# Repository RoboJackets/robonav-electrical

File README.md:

RoboNav Electrical
==========
Welcome to the electrcial repository of the RoboNav team! 

## Recommended Software (free)
- a [github account](https://github.com/join?source=header-home) 
    - the centralized location for all common files
- [git](https://git-scm.com/downloads)
    - popular version control system
    - quick [tutorial](https://try.github.io/levels/1/challenges/1)
- [EAGLE](https://www.autodesk.com/education/free-software/eagle)
    - CAD software for designing printed circuit boards (PCBs)

## Cloning the Repository
Now that you have all the required software, it's time to clone the repo!

To clone the repo, nagivate to the location in your computer where you would
like the repository using the change directory command in your terminal (cd):

```
cd desired-location
```

Now its time to clone:

```
git clone https://github.com/RoboJackets/robonav-electrical.git
```

You now have all you need to start contributing to the RoboNav Electrical team!

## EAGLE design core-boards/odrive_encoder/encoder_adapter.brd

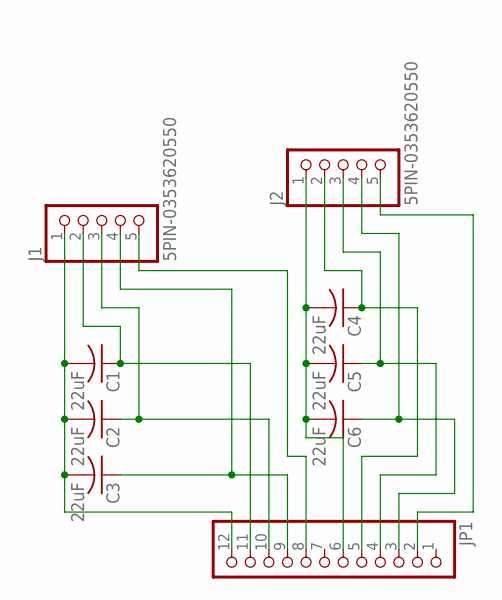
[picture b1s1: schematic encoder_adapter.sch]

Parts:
C1, C2, C3, C4, C5, C6: 22uF; C0805
J1, J2: 5PIN-0353620550; 0353620550
JP1: PINHD-1X12; 1X12

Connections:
unnamed: C1.2, C2.2, C3.2, J1.1, JP1.12
unnamed: C3.1, J1.4, JP1.9
unnamed: C1.1, J1.2, JP1.11
unnamed: C2.1, J1.3, JP1.10
unnamed: C4.1, J2.2, JP1.5
unnamed: C5.1, J2.3, JP1.4
unnamed: C6.1, J2.4, JP1.3
unnamed: J2.5, JP1.2
unnamed: J1.5, JP1.8
unnamed: C4.2, C5.2, C6.2, J2.1, JP1.6

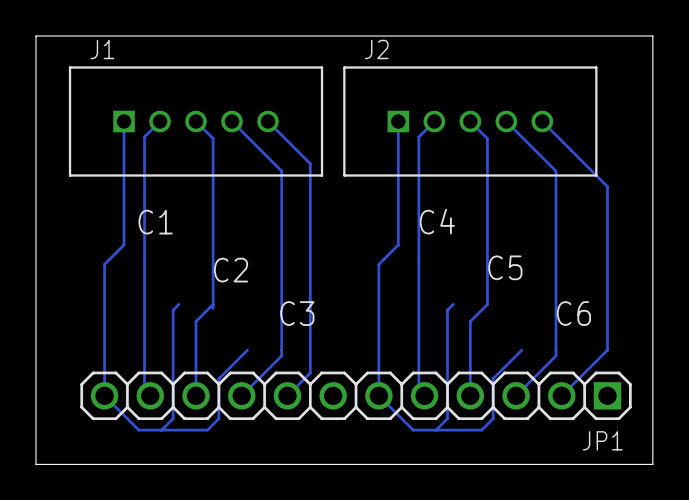
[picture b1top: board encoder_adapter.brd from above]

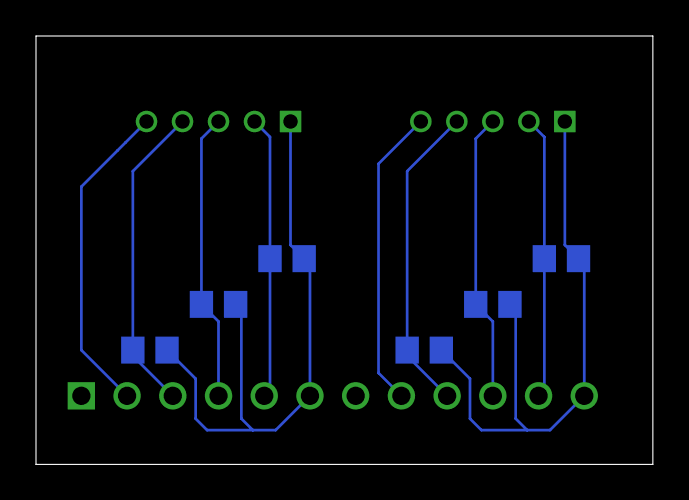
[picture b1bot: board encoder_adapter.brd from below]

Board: 1 copper layer, 34.3 x 23.8 mm, 9 parts (6 on the bottom side), 10 nets.

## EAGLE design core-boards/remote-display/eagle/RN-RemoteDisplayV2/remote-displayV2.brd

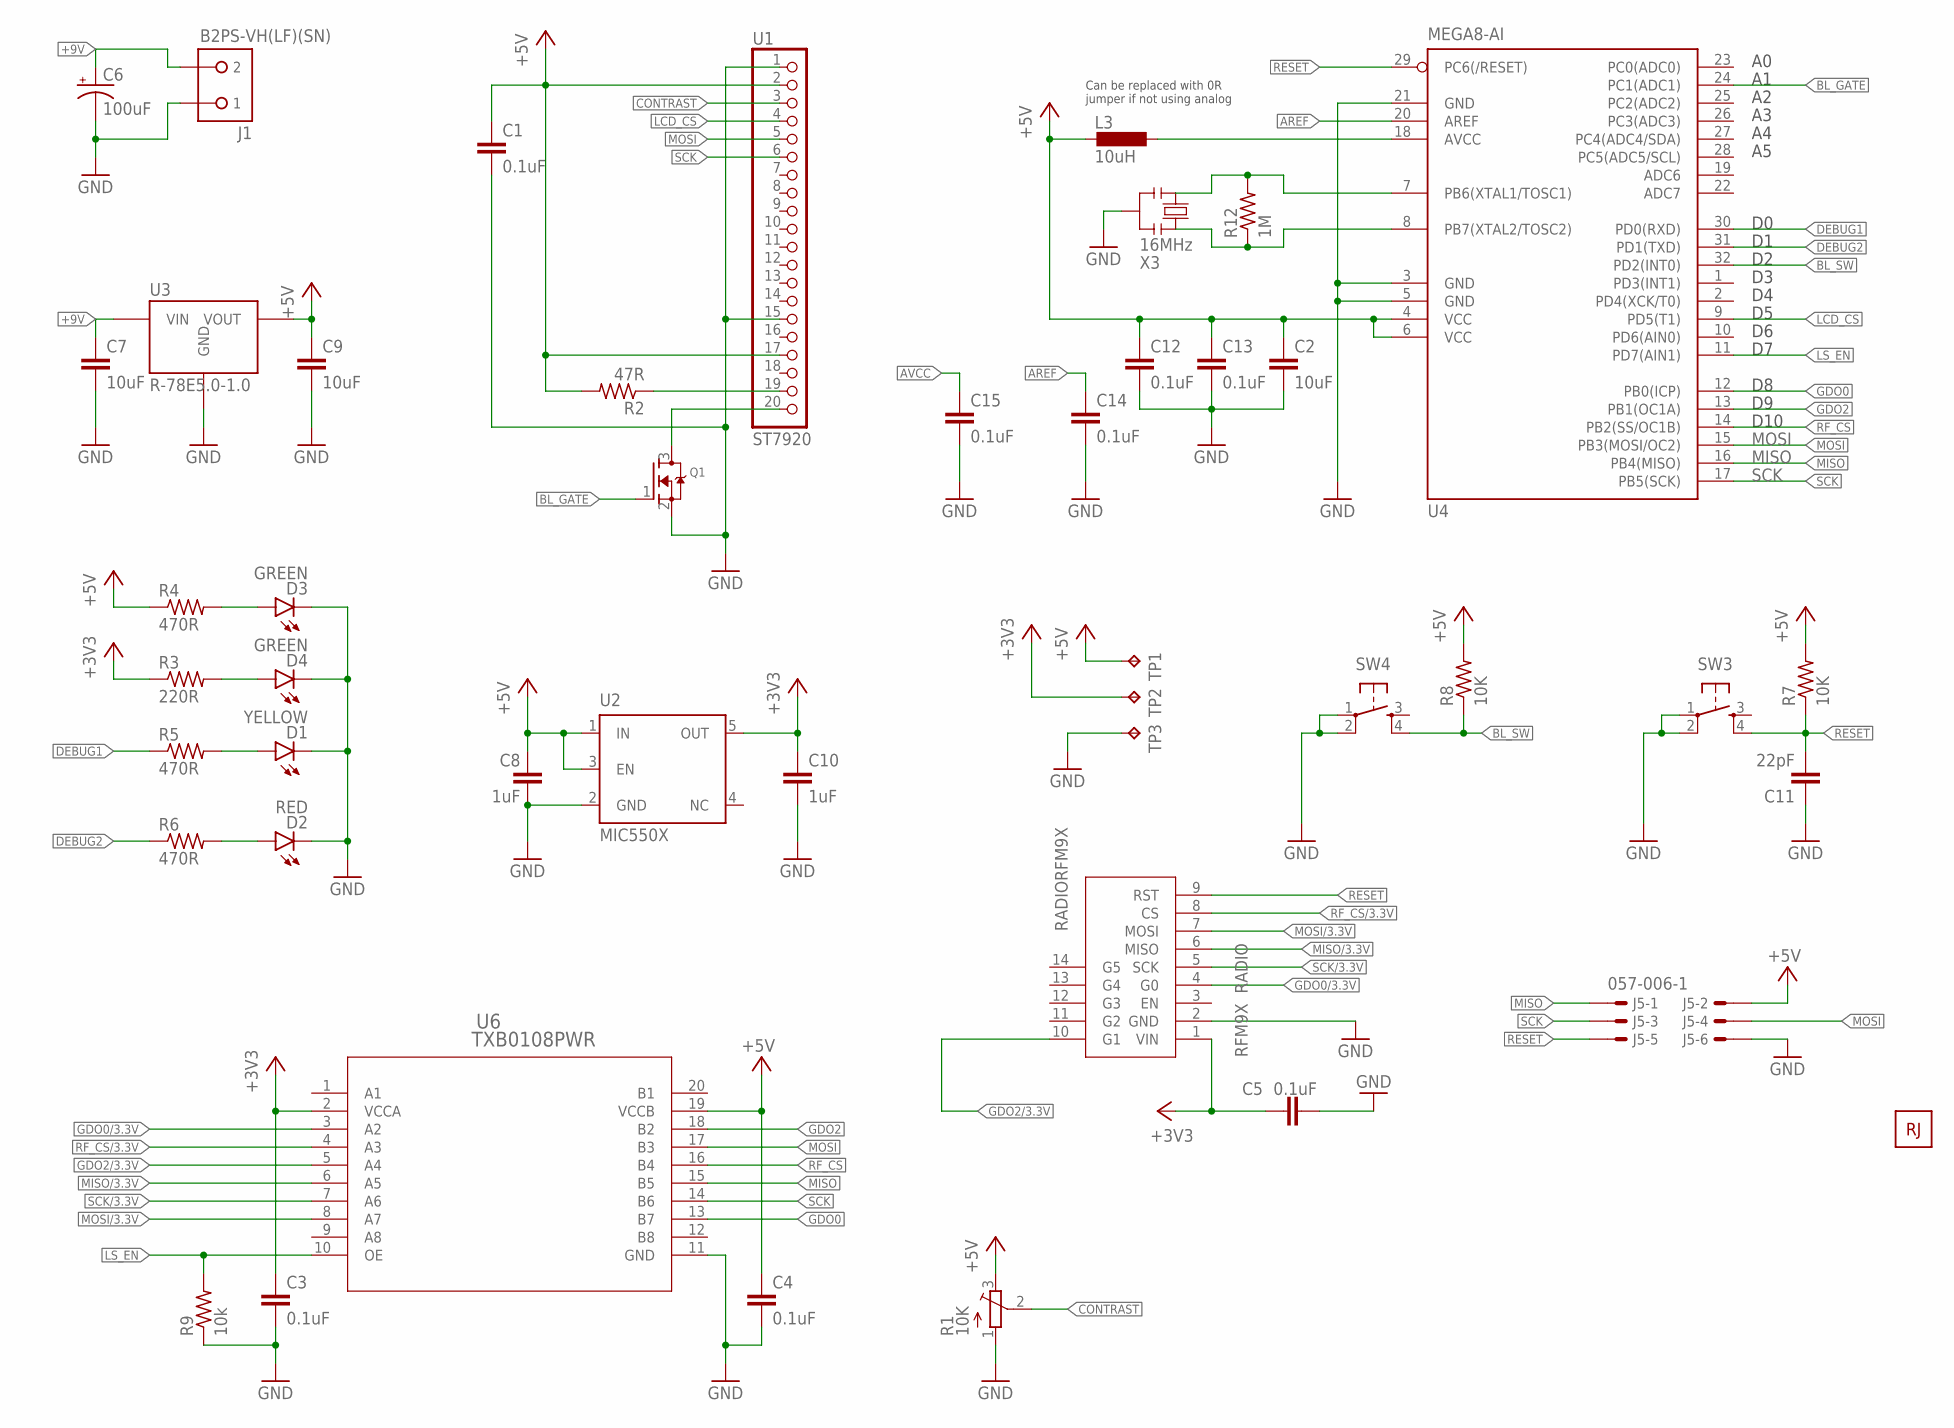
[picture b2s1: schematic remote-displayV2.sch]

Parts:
C1, C3, C4, C5, C12, C13, C14, C15: 0.1uF; C0603
C2: 10uF; C0805
C6: 100uF; E5-10,5
C7, C9: 10uF; C0603
C8, C10: 1uF; C0603
C11: 22pF; C0603
D1: YELLOW; LED3MM
D2: RED; LED3MM
D3, D4: GREEN; LED3MM
J1: B2PS-VH(LF)(SN); B2PS-CENTERED
J5: 057-006-1; DIGIKEY 3M15451-ND
L3: 10uH; 0805
Q1: MOSFET-NREFLOW; SOT23
R1: 10K; TRIM-3386
R2: 47R; R0805
R3: 220R; R0603
R4, R5, R6: 470R; R0603
R7, R8: 10K; R0603
R9: 10k; R0603
R12: 1M; R0603
SW3, SW4: TL1105_A-H
TP1, TP2, TP3: TPPAD1-17; P1-17
U1: ST7920; ST7920-LCD
U2: MIC550X; SOT23-DBV
U3: R-78E5.0-1.0; R-78E
U4: MEGA8-AI; TQFP32-08
U6: TXB0108PWR; PW20
U$1: RADIORFM9X; RFM9X
U$2: ROBOBUZZ1.0X; ROBOBUZZ_1.0X
X3: 16MHz; RESONATOR

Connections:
!RESET: C11.2, J5.5, R7.1, SW3.4, U4.29 (PC6(/RESET)), U$1.9 (RST)
!RF_CS!: U4.14 (PB2(SS/OC1B)), U6.16 (B4)
!RF_CS!/3.3V: U6.4 (A3), U$1.8 (CS)
+3V3: C3.1, C5.1, C10.1, R3.1, TP2.TP, U2.5 (OUT), U6.2 (VCCA), U$1.1 (VIN)
+5V: C1.1, C2.1, C4.1, C8.1, C9.1, C12.1, C13.1, J5.2, L3.2, R1.3 (E), R2.2, R4.1, R7.2, R8.2, TP1.TP, U1.2, U1.17, U2.1 (IN), U2.3 (EN), U3.3 (VOUT), U4.4 (VCC), U4.6 (VCC), U6.19 (VCCB)
+9V: C6.+, C7.1, J1.2, U3.1 (VIN)
AREF: C14.1, U4.20 (AREF)
AVCC: C15.1, L3.1, U4.18 (AVCC)
BL_DRAIN: Q1.3 (D), U1.20
BL_GATE: Q1.1 (G), U4.24 (PC1(ADC1))
BL_SW: R8.1, SW4.4, U4.32 (PD2(INT0))
CONTRAST: R1.2 (S), U1.3
DEBUG1: R5.1, U4.30 (PD0(RXD))
DEBUG2: R6.1, U4.31 (PD1(TXD))
GDO0: U4.12 (PB0(ICP)), U6.13 (B7)
GDO0/3.3V: U6.3 (A2), U$1.4 (G0)
GDO2: U4.13 (PB1(OC1A)), U6.18 (B2)
GDO2/3.3V: U6.5 (A4), U$1.10 (G1)
GND: C1.2, C2.2, C3.2, C4.2, C5.2, C6.-, C7.2, C8.2, C9.2, C10.2, C11.1, C12.2, C13.2, C14.2, C15.2, D1.K (C), D2.K (C), D3.K (C), D4.K (C), J1.1, J5.6, Q1.2 (S), R1.1 (A), R9.1, SW3.1, SW3.2, SW4.1, SW4.2, TP3.TP, U1.1, U1.15, U2.2 (GND), U3.2 (GND), U4.3 (GND), U4.5 (GND), U4.21 (GND), U6.11 (GND), U$1.2 (GND), X3.2
LCD_BL: R2.1, U1.19
LCD_CS: U1.4, U4.9 (PD5(T1))
LS_EN: R9.2, U4.11 (PD7(AIN1)), U6.10 (OE)
MISO: J5.1, U4.16 (PB4(MISO)), U6.15 (B5)
MISO/3.3V: U6.6 (A5), U$1.6 (MISO)
MOSI: J5.4, U1.5, U4.15 (PB3(MOSI/OC2)), U6.17 (B3)
MOSI/3.3V: U6.8 (A7), U$1.7 (MOSI)
PWR_LED: D3.A, R4.2
PWR_LED1: D4.A, R3.2
SCK: J5.3, U1.6, U4.17 (PB5(SCK)), U6.14 (B6)
SCK/3.3V: U6.7 (A6), U$1.5 (SCK)
STAT1_LED: D1.A, R5.2
STAT2_LED: D2.A, R6.2
XTAL1: R12.2, U4.7 (PB6(XTAL1/TOSC1)), X3.1
XTAL2: R12.1, U4.8 (PB7(XTAL2/TOSC2)), X3.3

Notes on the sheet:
D10
Can be replaced with 0R jumper if not using analog

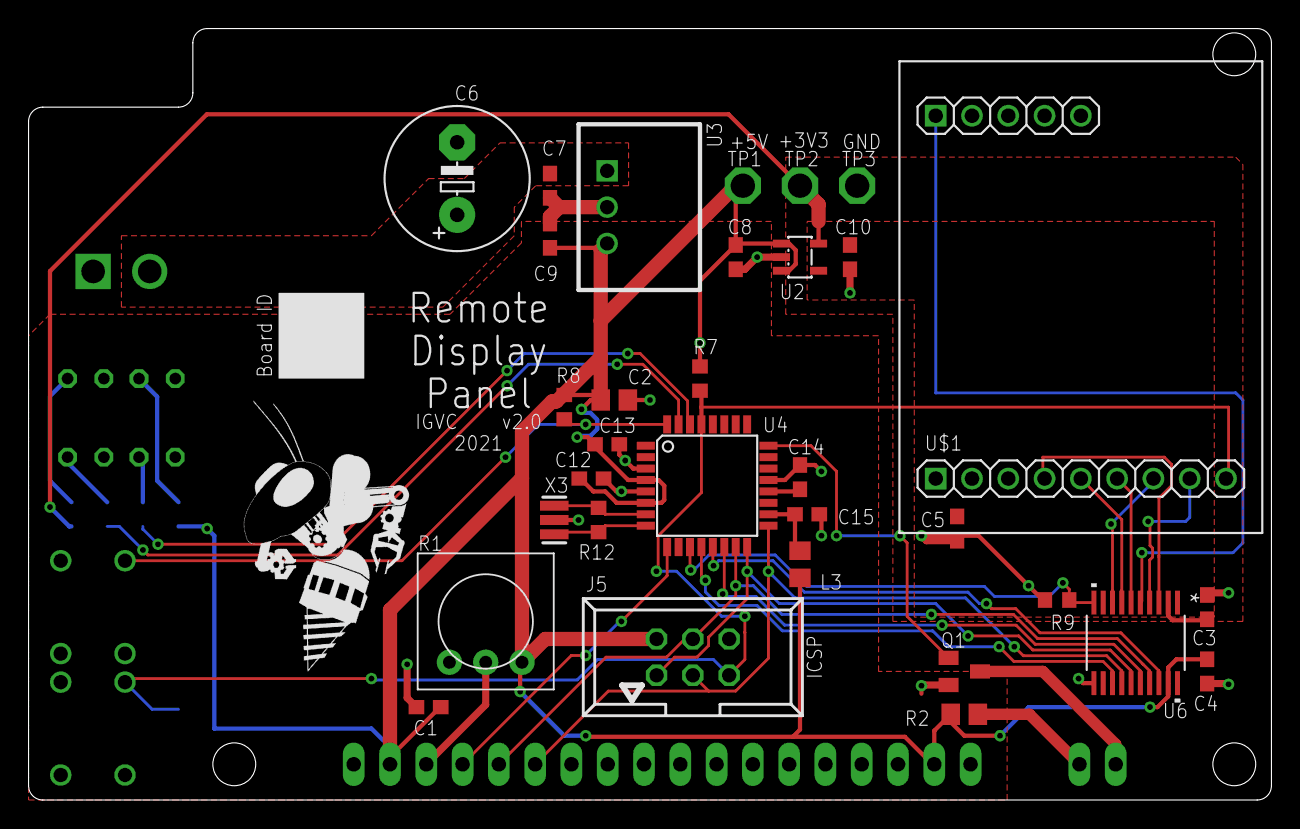
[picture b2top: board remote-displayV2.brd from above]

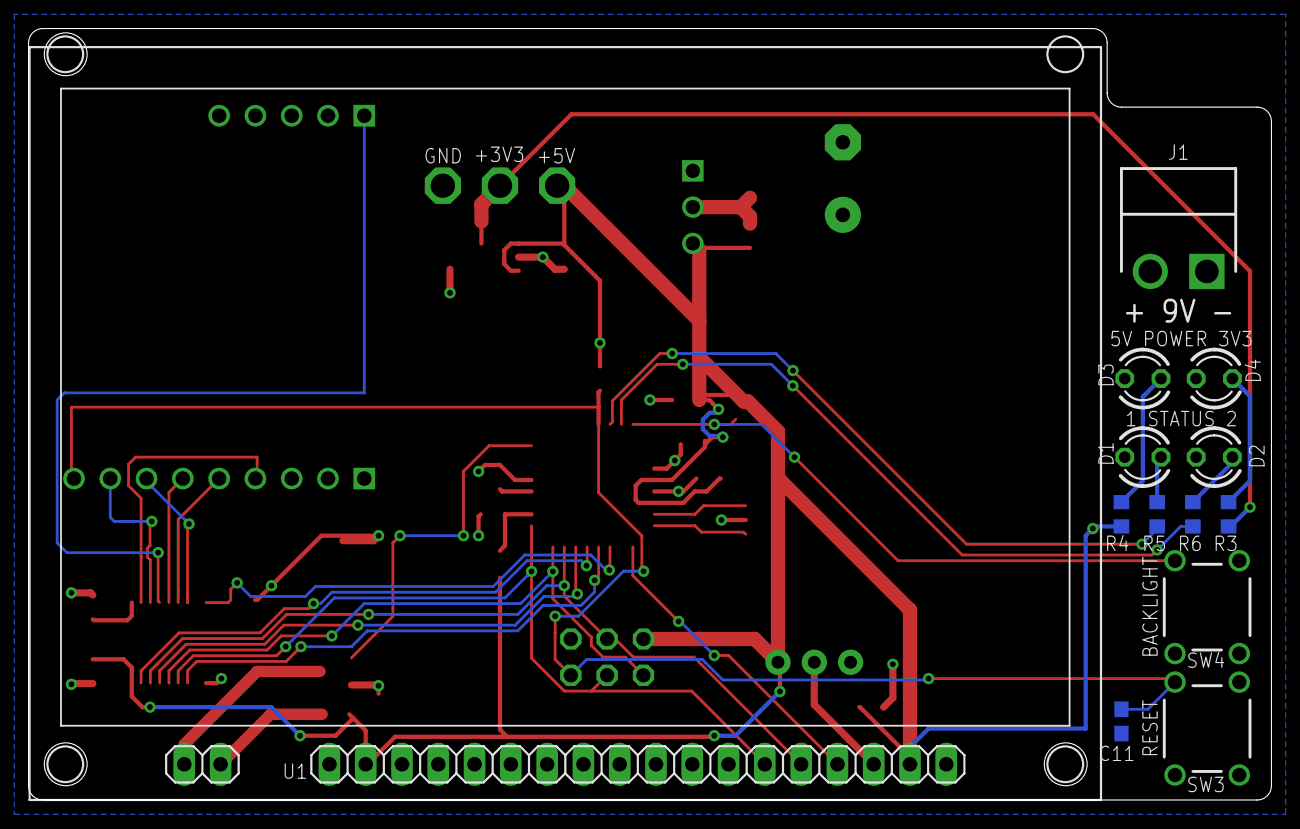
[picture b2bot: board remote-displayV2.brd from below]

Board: 2 copper layers, 87.0 x 54.0 mm, 46 parts (13 on the bottom side), 34 nets.

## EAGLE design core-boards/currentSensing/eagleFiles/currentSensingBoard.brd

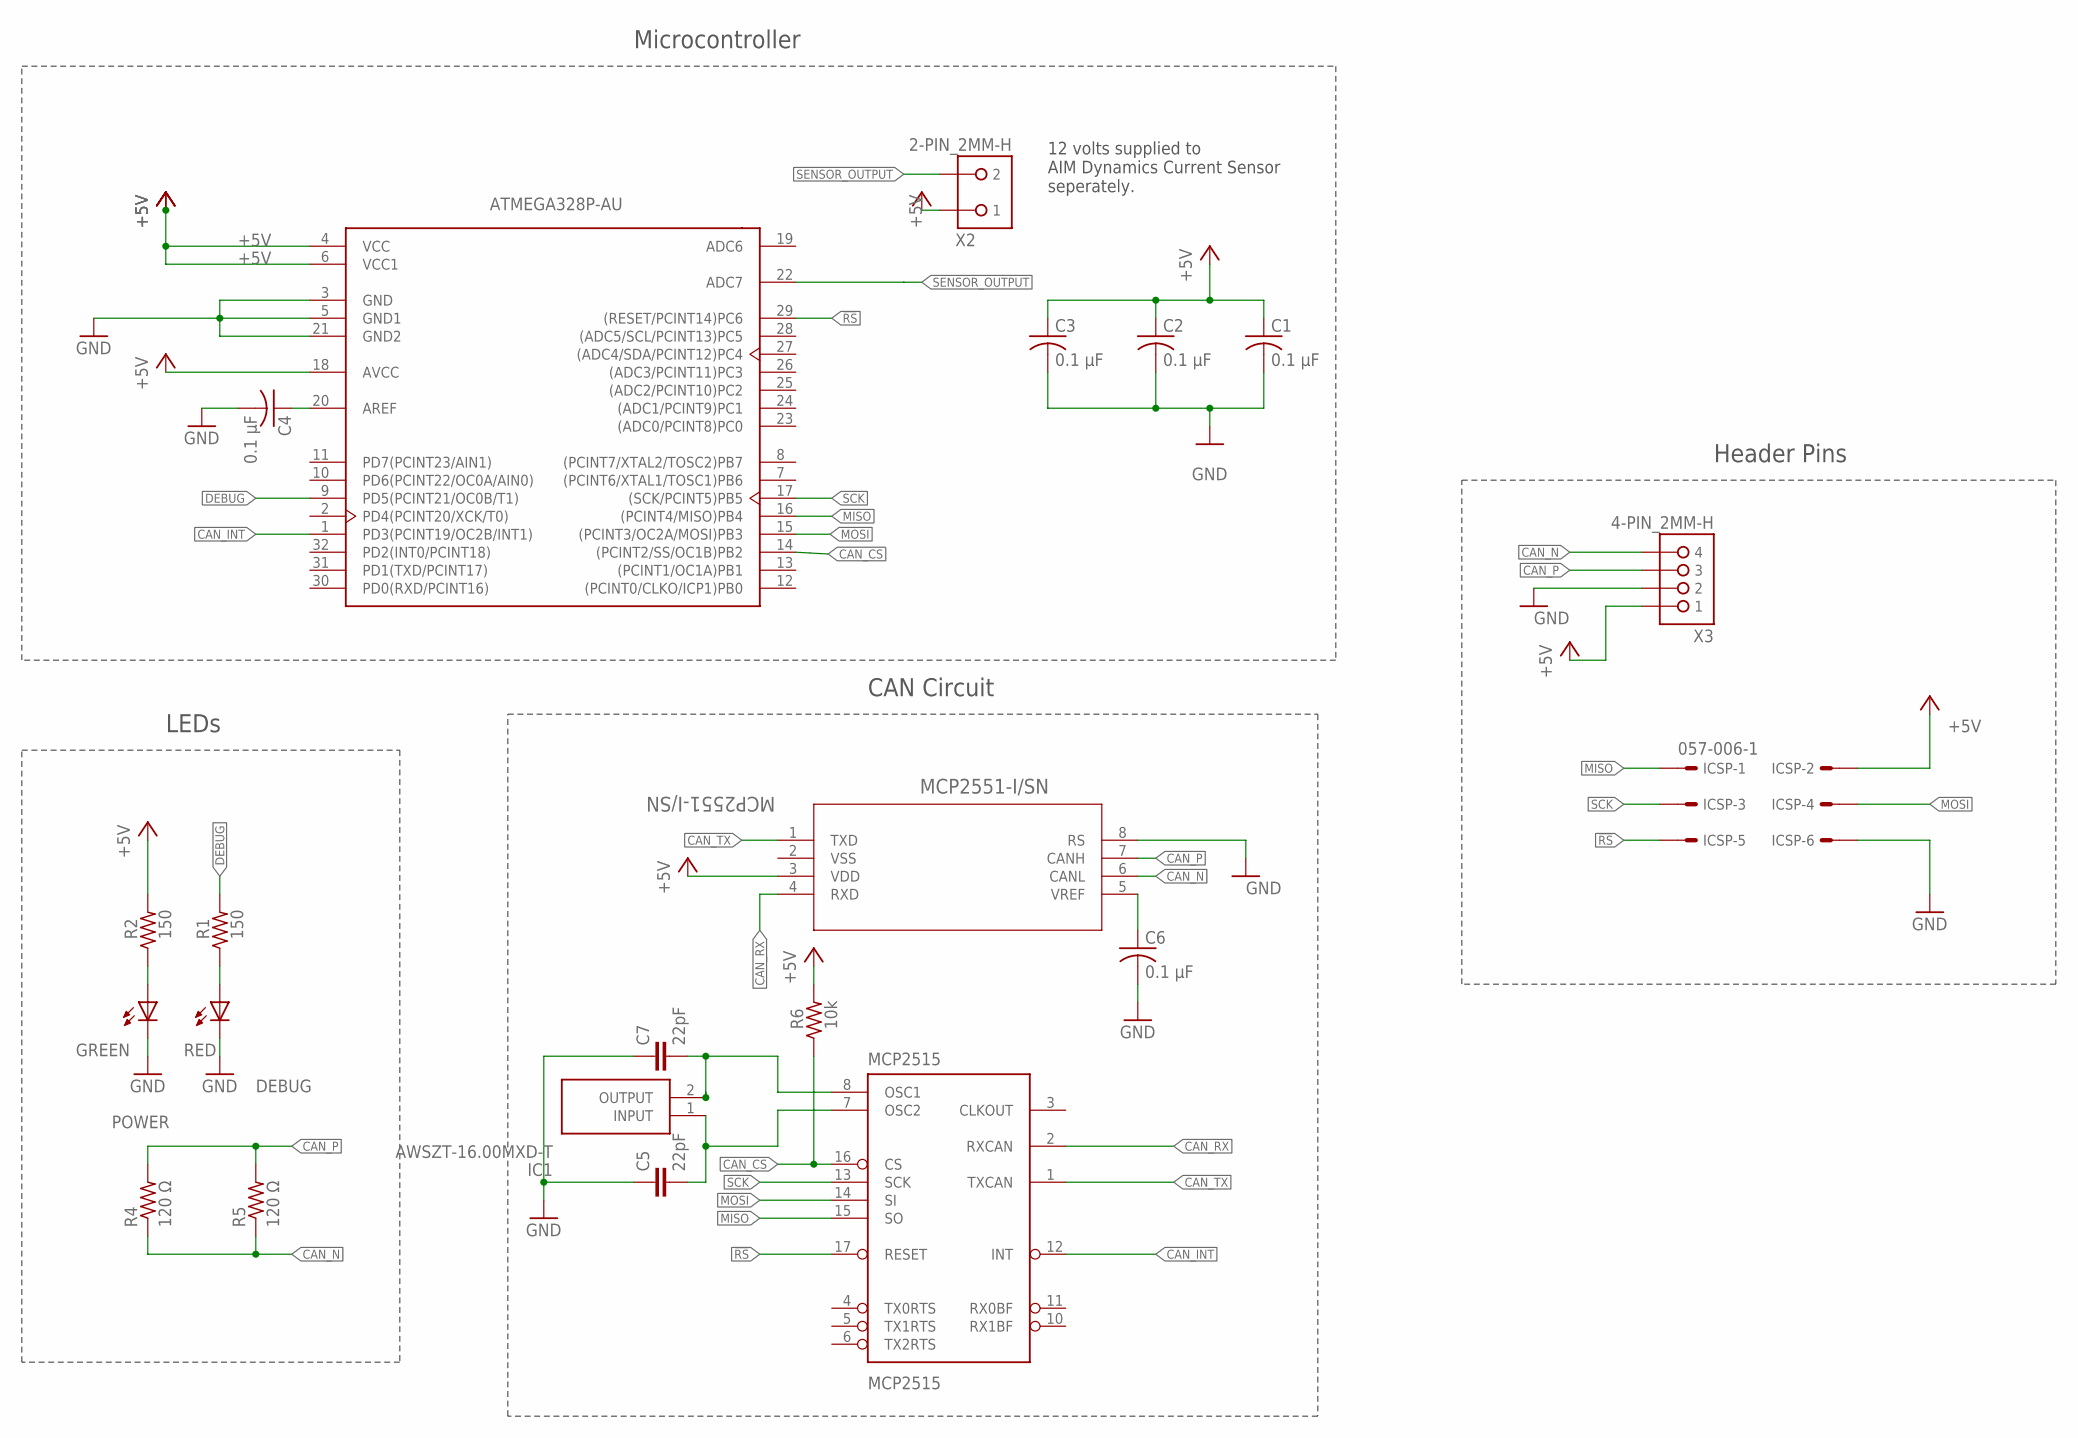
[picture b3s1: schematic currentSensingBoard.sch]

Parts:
ATMEGA328P-AU(V1): ATMEGA328P-AU (V1); TQFP-32; PARTS_NAME ATMEGA328P-AU
C1, C2, C3, C4, C6: 0.1 µF; C0603
C5, C7: 22pF; 0603-CAP
DEBUG: RED; CHIP-LED0603
IC1: AWSZT-16.00MXD-T; AWSZT1600MXDT
ICSP: 057-006-1
MCP2515: MCP2515; SO-18W
MCP2551-I/SN: MCP2551-I/SN; SOIC8-N_MC
POWER: GREEN; CHIP-LED0603
R1, R2: 150; R0603
R4, R5: 120 Ω; R0603
R6: 10k; R0603
X2: 2-PIN_2MM-H; 2MM-2-H
X3: 4-PIN_2MM-H; 2MM-4-H

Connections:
!RS: ATMEGA328P-AU(V1).29 ((RESET/PCINT14)PC6), ICSP.5, MCP2515.17 (RESET)
+5V: ATMEGA328P-AU(V1).4 (VCC), ATMEGA328P-AU(V1).6 (VCC1), ATMEGA328P-AU(V1).18 (AVCC), C1.1, C2.1, C3.1, ICSP.2, MCP2551-I/SN.3 (VDD), R2.2, R6.2, X2.1, X3.1
CAN_CS: ATMEGA328P-AU(V1).14 ((PCINT2/SS/OC1B)PB2), MCP2515.16 (CS), R6.1
CAN_INT: ATMEGA328P-AU(V1).1 (PD3(PCINT19/OC2B/INT1)), MCP2515.12 (INT)
CAN_N: MCP2551-I/SN.6 (CANL), R4.1, R5.1, X3.4
CAN_P: MCP2551-I/SN.7 (CANH), R4.2, R5.2, X3.3
CAN_RX: MCP2515.2 (RXCAN), MCP2551-I/SN.4 (RXD)
CAN_TX: MCP2515.1 (TXCAN), MCP2551-I/SN.1 (TXD)
CLK1: C5.2, IC1.1 (INPUT), MCP2515.7 (OSC2)
CLK2: C7.2, IC1.2 (OUTPUT), MCP2515.8 (OSC1)
DEBUG: ATMEGA328P-AU(V1).9 (PD5(PCINT21/OC0B/T1)), R1.2
GND: ATMEGA328P-AU(V1).3 (GND), ATMEGA328P-AU(V1).5 (GND1), ATMEGA328P-AU(V1).21 (GND2), C1.2, C2.2, C3.2, C4.2, C5.1, C6.2, C7.1, DEBUG.C (K), ICSP.6, MCP2551-I/SN.8 (RS), POWER.C (K), X3.2
MISO: ATMEGA328P-AU(V1).16 ((PCINT4/MISO)PB4), ICSP.1, MCP2515.15 (SO)
MOSI: ATMEGA328P-AU(V1).15 ((PCINT3/OC2A/MOSI)PB3), ICSP.4, MCP2515.14 (SI)
unnamed: DEBUG.A, R1.1
unnamed: C6.1, MCP2551-I/SN.5 (VREF)
unnamed: ATMEGA328P-AU(V1).20 (AREF), C4.1
unnamed: POWER.A, R2.1
SCK: ATMEGA328P-AU(V1).17 ((SCK/PCINT5)PB5), ICSP.3, MCP2515.13 (SCK)
SENSOR_OUTPUT: ATMEGA328P-AU(V1).22 (ADC7), X2.2
VDD: MCP2515.18 (VDD)
VSS: MCP2515.9 (VSS)

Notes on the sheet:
CAN Circuit
12 volts supplied to AIM Dynamics Current Sensor seperately.
LEDs
Header Pins
Microcontroller

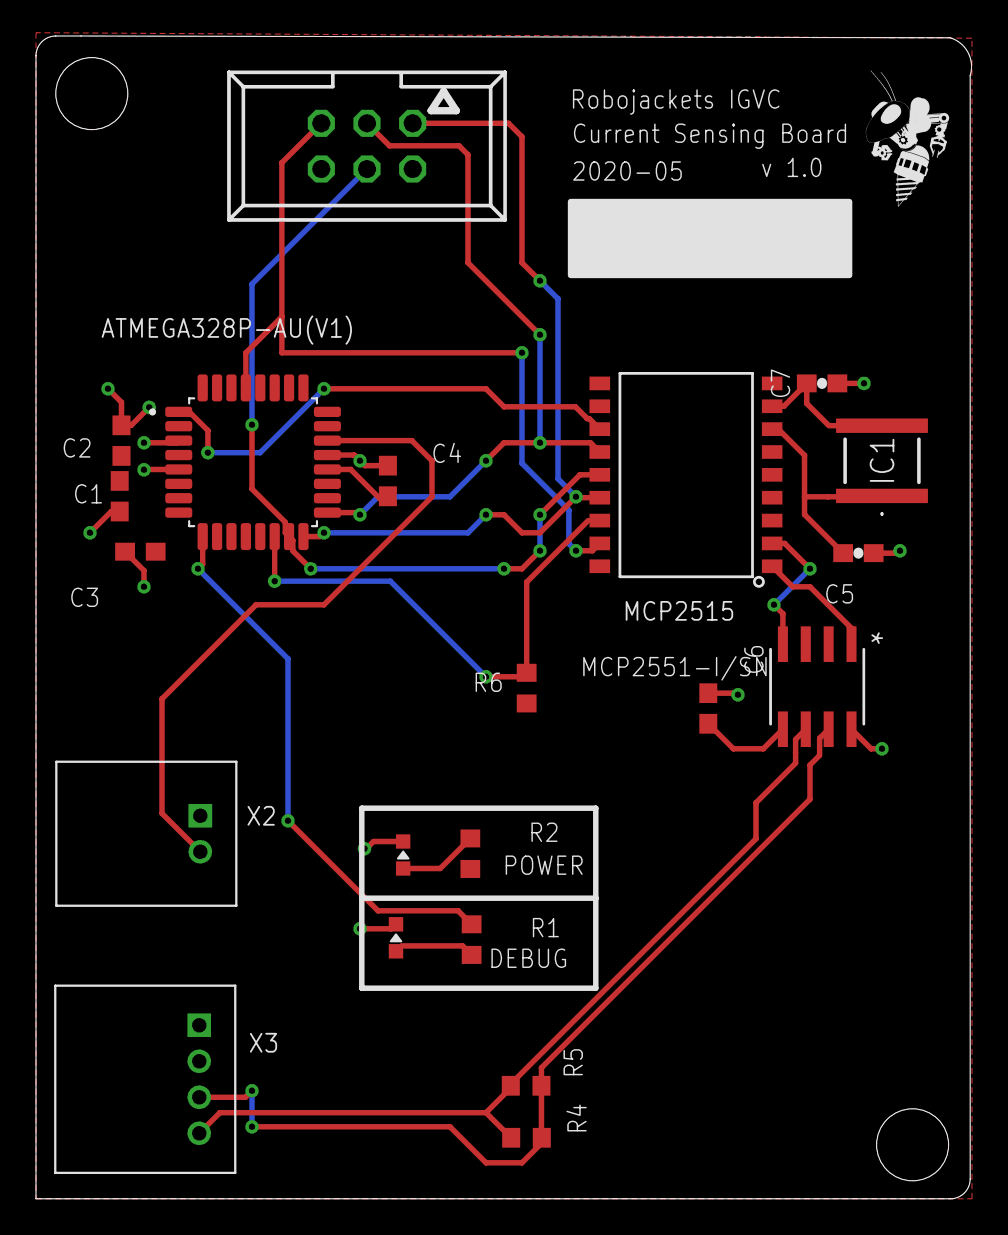
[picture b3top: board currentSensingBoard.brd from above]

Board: 2 copper layers, 52.0 x 64.6 mm, 22 parts (0 on the bottom side), 20 nets.

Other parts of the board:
U$1: ROBOBUZZ_0.4X

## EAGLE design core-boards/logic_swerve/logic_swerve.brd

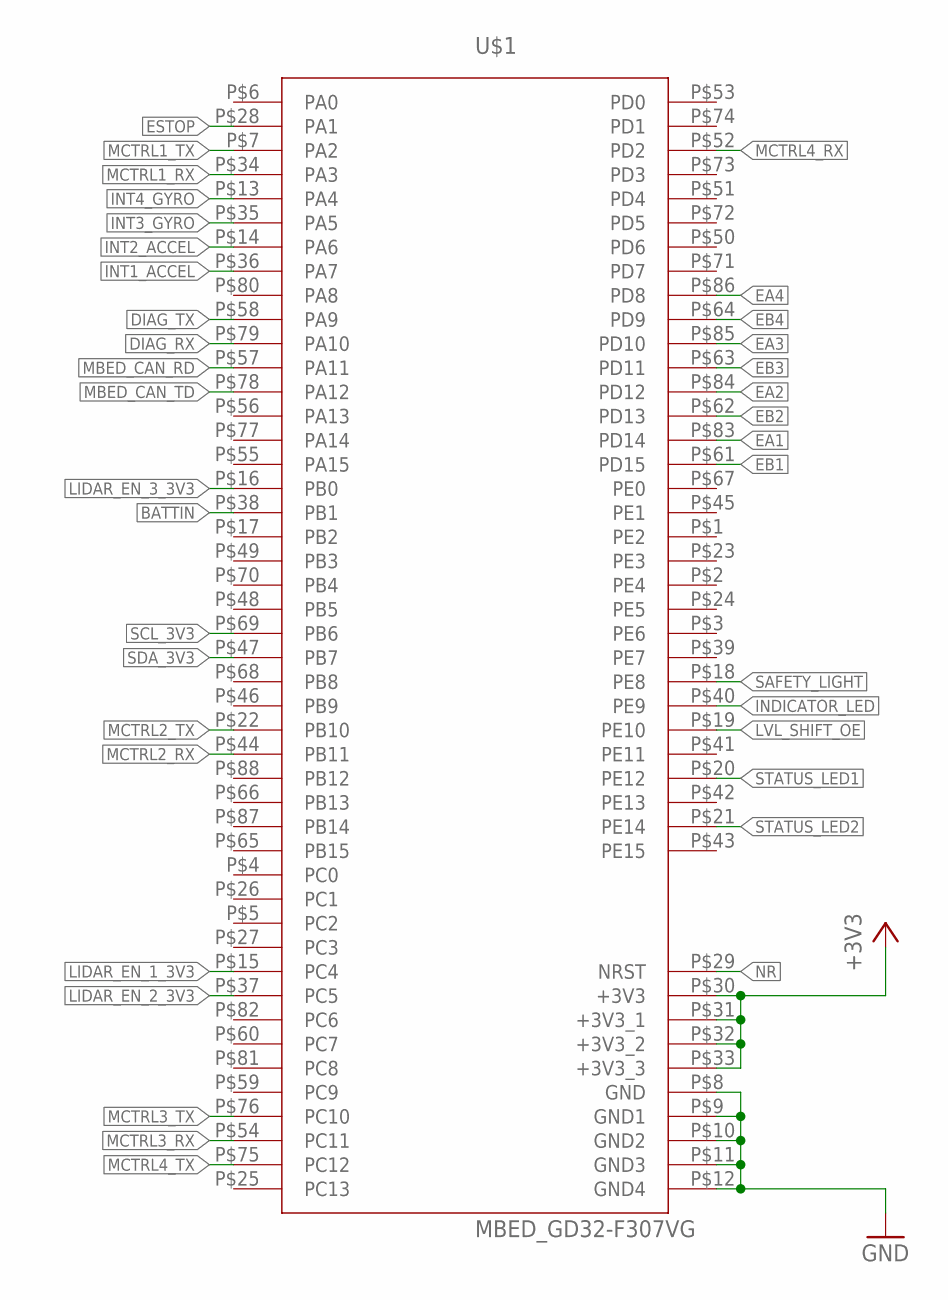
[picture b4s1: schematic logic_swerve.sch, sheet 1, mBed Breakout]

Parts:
U$1: MBED_GD32-F307VG; SWERVE_MBED

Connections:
+3V3: U$1.P$30 (+3V3), U$1.P$31 (+3V3_1), U$1.P$32 (+3V3_2), U$1.P$33 (+3V3_3); also elsewhere on the board
BATTIN: U$1.P$38 (PB1); also elsewhere on the board
DIAG_RX: U$1.P$79 (PA10); also elsewhere on the board
DIAG_TX: U$1.P$58 (PA9); also elsewhere on the board
EA1: U$1.P$83 (PD14); also elsewhere on the board
EA2: U$1.P$84 (PD12); also elsewhere on the board
EA3: U$1.P$85 (PD10); also elsewhere on the board
EA4: U$1.P$86 (PD8); also elsewhere on the board
EB1: U$1.P$61 (PD15); also elsewhere on the board
EB2: U$1.P$62 (PD13); also elsewhere on the board
EB3: U$1.P$63 (PD11); also elsewhere on the board
EB4: U$1.P$64 (PD9); also elsewhere on the board
ESTOP: U$1.P$28 (PA1); also elsewhere on the board
GND: U$1.P$8 (GND), U$1.P$9 (GND1), U$1.P$10 (GND2), U$1.P$11 (GND3), U$1.P$12 (GND4); also elsewhere on the board
INDICATOR_LED: U$1.P$40 (PE9); also elsewhere on the board
INT1_ACCEL: U$1.P$36 (PA7)
INT2_ACCEL: U$1.P$14 (PA6)
INT3_GYRO: U$1.P$35 (PA5)
INT4_GYRO: U$1.P$13 (PA4)
LIDAR_EN_1_3V3: U$1.P$15 (PC4); also elsewhere on the board
LIDAR_EN_2_3V3: U$1.P$37 (PC5); also elsewhere on the board
LIDAR_EN_3_3V3: U$1.P$16 (PB0); also elsewhere on the board
LVL_SHIFT_OE: U$1.P$19 (PE10); also elsewhere on the board
MBED_CAN_RD: U$1.P$57 (PA11); also elsewhere on the board
MBED_CAN_TD: U$1.P$78 (PA12); also elsewhere on the board
MCTRL1_RX: U$1.P$34 (PA3); also elsewhere on the board
MCTRL1_TX: U$1.P$7 (PA2); also elsewhere on the board
MCTRL2_RX: U$1.P$44 (PB11); also elsewhere on the board
MCTRL2_TX: U$1.P$22 (PB10); also elsewhere on the board
MCTRL3_RX: U$1.P$54 (PC11); also elsewhere on the board
MCTRL3_TX: U$1.P$76 (PC10); also elsewhere on the board
MCTRL4_RX: U$1.P$52 (PD2); also elsewhere on the board
MCTRL4_TX: U$1.P$75 (PC12); also elsewhere on the board
NR: U$1.P$29 (NRST); also elsewhere on the board
SAFETY_LIGHT: U$1.P$18 (PE8); also elsewhere on the board
SCL_3V3: U$1.P$69 (PB6); also elsewhere on the board
SDA_3V3: U$1.P$47 (PB7); also elsewhere on the board
STATUS_LED1: U$1.P$20 (PE12); also elsewhere on the board
STATUS_LED2: U$1.P$21 (PE14); also elsewhere on the board

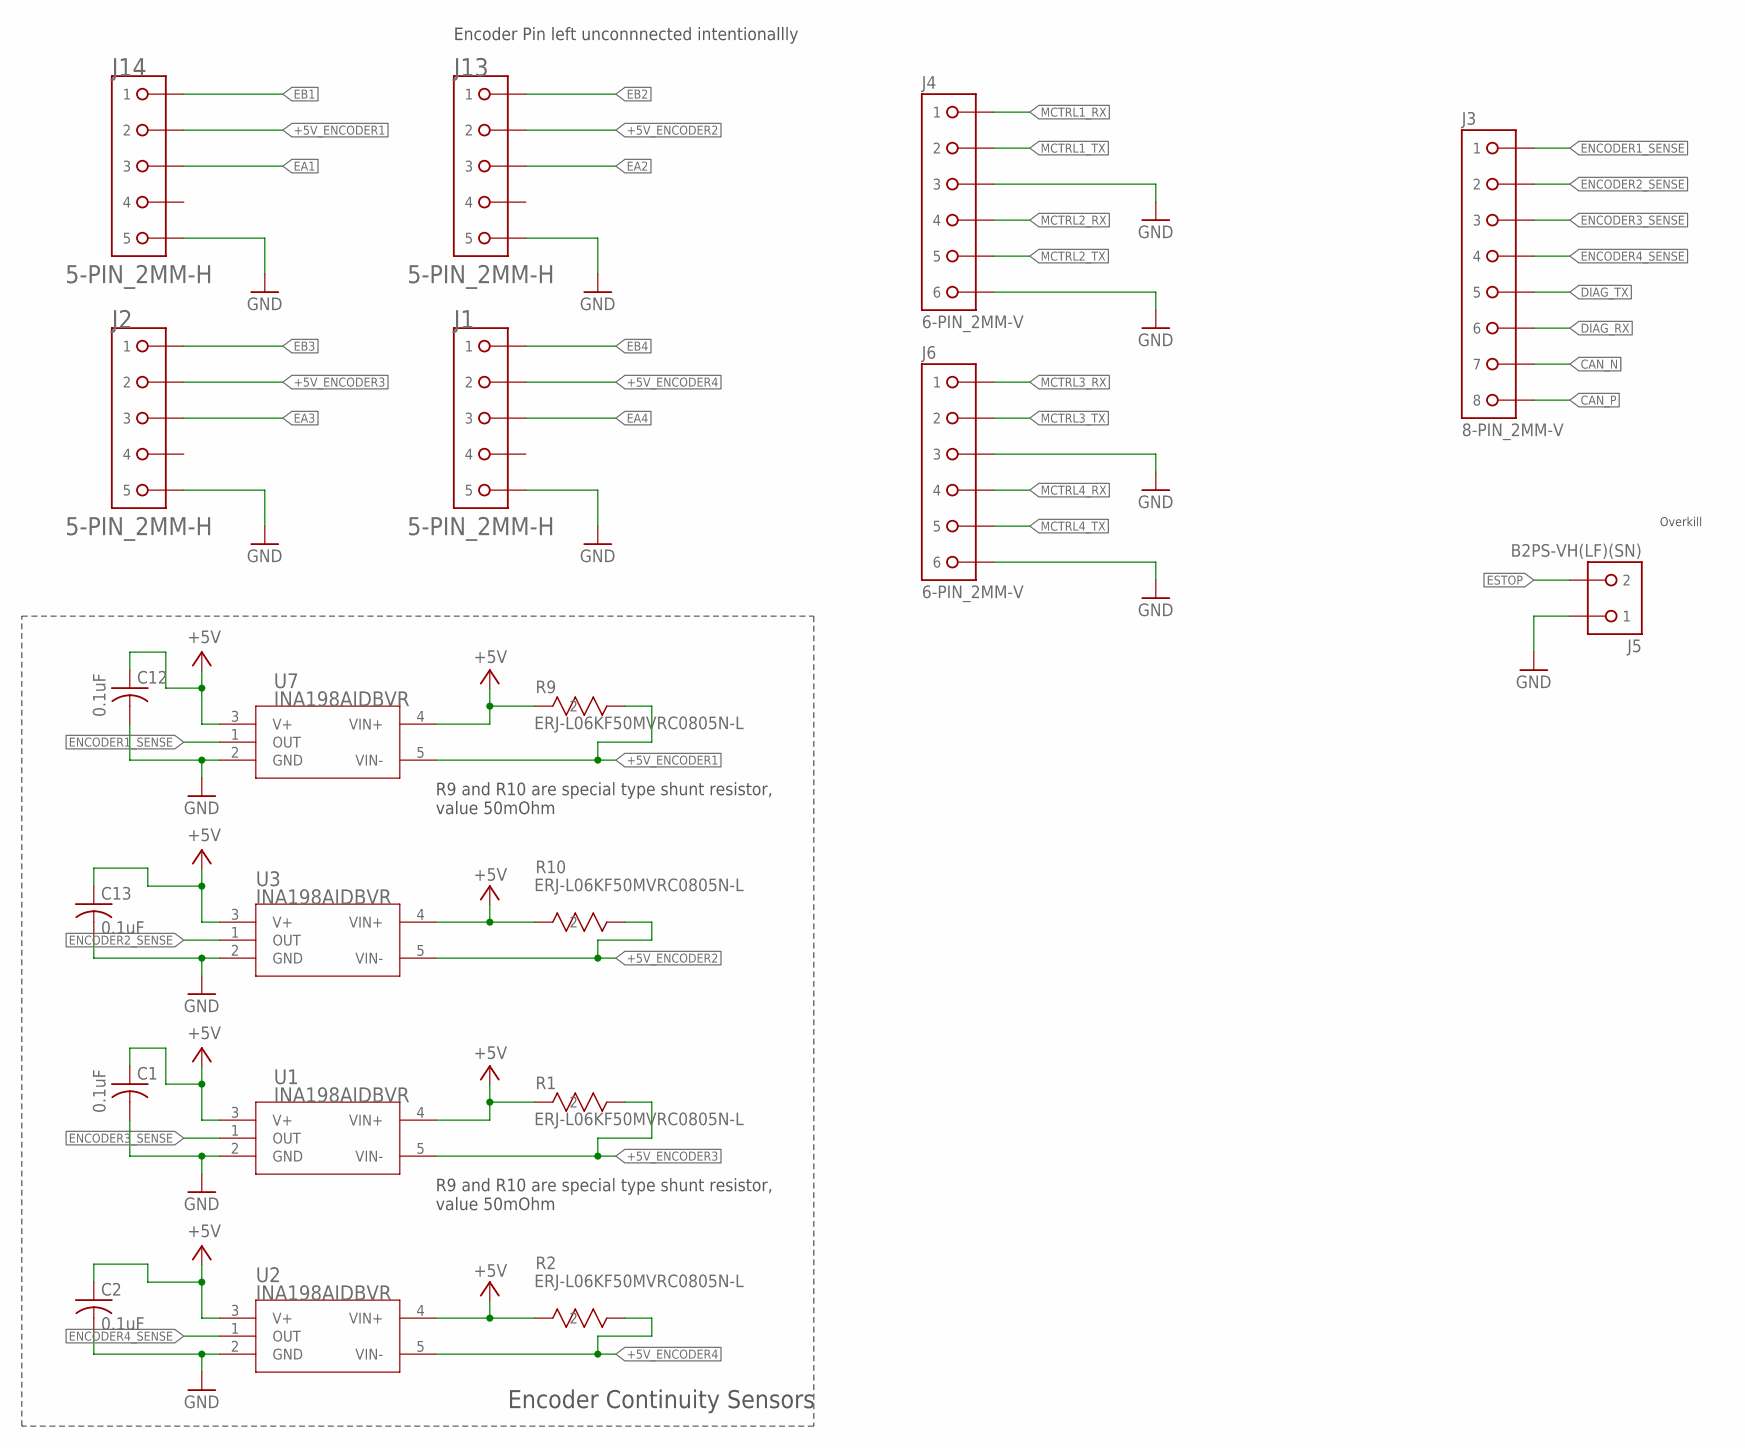
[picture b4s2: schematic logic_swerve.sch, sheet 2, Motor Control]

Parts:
C1, C2, C12, C13: 0.1uF; C0603
J1, J2, J13, J14: 5-PIN_2MM-H; 2MM-5-H
J3: 8-PIN_2MM-V; 2MM-8-V
J4, J6: 6-PIN_2MM-V; 2MM-6-V
J5: B2PS-VH(LF)(SN); B2PS-CENTERED
R1, R2, R9, R10: ERJ-L06KF50MVRC0805N-L; RC0805N-L
U1, U2, U3, U7: INA198AIDBVR; DBV5

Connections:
+5V: C1.1, C2.1, C12.1, C13.1, R1.2, R2.2, R9.2, R10.2, U1.3 (V+), U1.4 (VIN+), U2.3 (V+), U2.4 (VIN+), U3.3 (V+), U3.4 (VIN+), U7.3 (V+), U7.4 (VIN+); also elsewhere on the board
+5V_ENCODER1: J14.2, R9.1, U7.5 (VIN-)
+5V_ENCODER2: J13.2, R10.1, U3.5 (VIN-)
+5V_ENCODER3: J2.2, R1.1, U1.5 (VIN-)
+5V_ENCODER4: J1.2, R2.1, U2.5 (VIN-)
CAN_N: J3.7; also elsewhere on the board
CAN_P: J3.8; also elsewhere on the board
DIAG_RX: J3.6; also elsewhere on the board
DIAG_TX: J3.5; also elsewhere on the board
EA1: J14.3; also elsewhere on the board
EA2: J13.3; also elsewhere on the board
EA3: J2.3; also elsewhere on the board
EA4: J1.3; also elsewhere on the board
EB1: J14.1; also elsewhere on the board
EB2: J13.1; also elsewhere on the board
EB3: J2.1; also elsewhere on the board
EB4: J1.1; also elsewhere on the board
ENCODER1_SENSE: J3.1, U7.1 (OUT)
ENCODER2_SENSE: J3.2, U3.1 (OUT)
ENCODER3_SENSE: J3.3, U1.1 (OUT)
ENCODER4_SENSE: J3.4, U2.1 (OUT)
ESTOP: J5.2; also elsewhere on the board
GND: C1.2, C2.2, C12.2, C13.2, J1.5, J2.5, J4.3, J4.6, J5.1, J6.3, J6.6, J13.5, J14.5, U1.2 (GND), U2.2 (GND), U3.2 (GND), U7.2 (GND); also elsewhere on the board
MCTRL1_RX: J4.1; also elsewhere on the board
MCTRL1_TX: J4.2; also elsewhere on the board
MCTRL2_RX: J4.4; also elsewhere on the board
MCTRL2_TX: J4.5; also elsewhere on the board
MCTRL3_RX: J6.1; also elsewhere on the board
MCTRL3_TX: J6.2; also elsewhere on the board
MCTRL4_RX: J6.4; also elsewhere on the board
MCTRL4_TX: J6.5; also elsewhere on the board

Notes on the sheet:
Encoder Pin left unconnnected intentionallly
Encoder Continuity Sensors
R9 and R10 are special type shunt resistor, value 50mOhm
Overkill

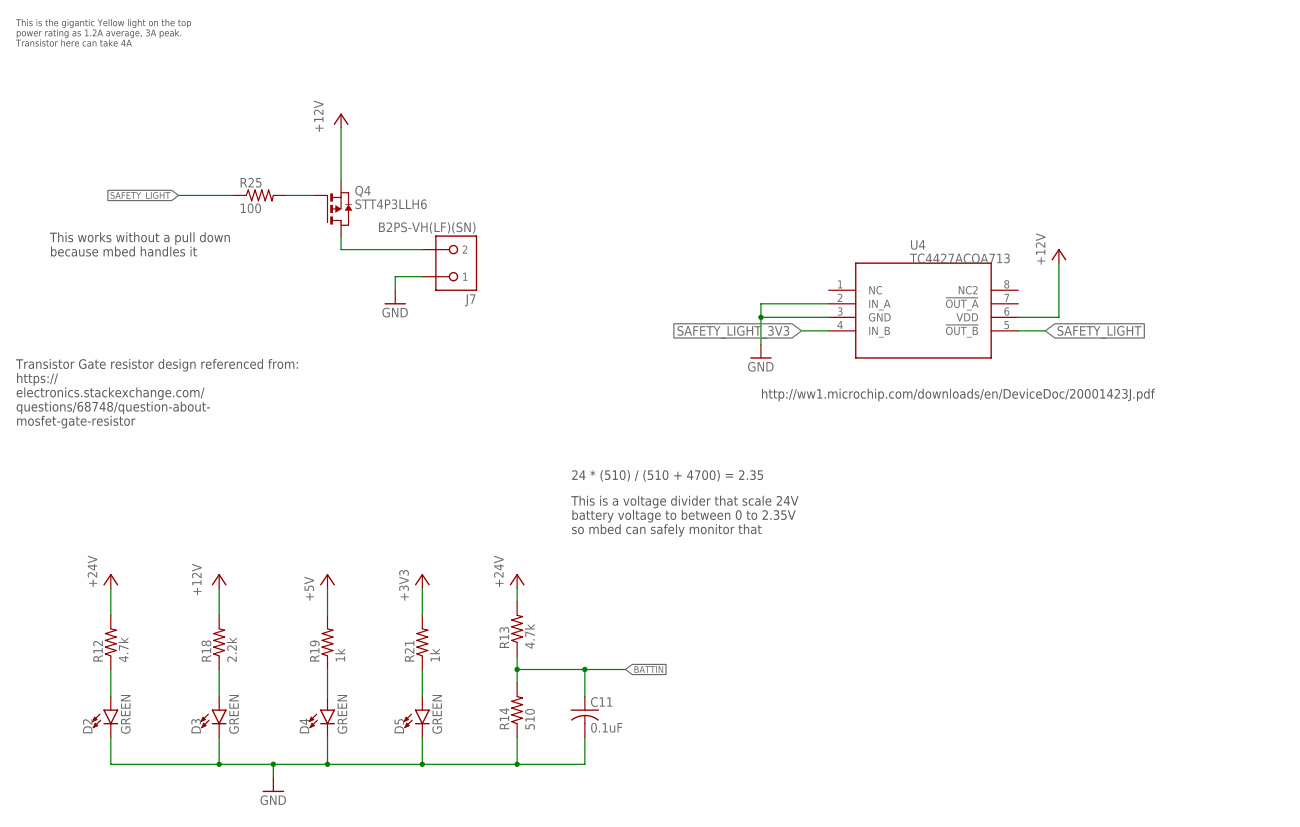
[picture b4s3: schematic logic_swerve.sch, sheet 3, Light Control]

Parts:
C11: 0.1uF; C0603
D2, D3, D4, D5: GREEN; LED-0603
J7: B2PS-VH(LF)(SN); B2PS-CENTERED
Q4: STT4P3LLH6; SOT23-6
R12, R13: 4.7k; R0603
R14: 510; R0603
R18: 2.2k; R0603
R19, R21: 1k; R0603
R25: 100; R0603
U4: TC4427ACOA713; SOIC-8

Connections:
3V3_LED_R: D5.A, R21.1
5V_LED_R: D4.A, R19.1
12V_LED_R: D3.A, R18.1
+3V3: R21.2; also elsewhere on the board
+5V: R19.2; also elsewhere on the board
+12V: Q4.4 (S), R18.2, U4.6 (VDD); also elsewhere on the board
+24V: R12.2, R13.2; also elsewhere on the board
BATTIN: C11.1, R13.1, R14.2; also elsewhere on the board
GND: C11.2, D2.C, D3.C, D4.C, D5.C, J7.1, R14.1, U4.2 (IN_A), U4.3 (GND); also elsewhere on the board
unnamed: D2.A, R12.1
SAFETY_HRD: J7.2, Q4.1 (D), Q4.2 (D), Q4.5 (D), Q4.6 (D)
SAFETY_LIGHT: R25.1, U4.5 (!OUT_B); also elsewhere on the board
SAFETY_LIGHT_3V3: U4.4 (IN_B)
SAFETY_R: Q4.3 (G), R25.2

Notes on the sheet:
This is the gigantic Yellow light on the top power rating as 1.2A average, 3A peak. Transistor here can take 4A
24 * (510) / (510 + 4700) = 2.35
Transistor Gate resistor design referenced from: https:// electronics.stackexchange.com/ questions/68748/question-about- mosfet-gate-resistor
http://ww1.microchip.com/downloads/en/DeviceDoc/20001423J.pdf
This is a voltage divider that scale 24V battery voltage to between 0 to 2.35V so mbed can safely monitor that
This works without a pull down because mbed handles it

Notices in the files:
parts and their libraries:
SparkFun-Capacitors: Licensing: Creative Commons ShareAlike 4.0 International - https://creativecommons.org/licenses/by-sa/4.0
SparkFun-Aesthetics: Licensing: CC v3.0 Share-Alike You are welcome to use this library for commercial purposes.
